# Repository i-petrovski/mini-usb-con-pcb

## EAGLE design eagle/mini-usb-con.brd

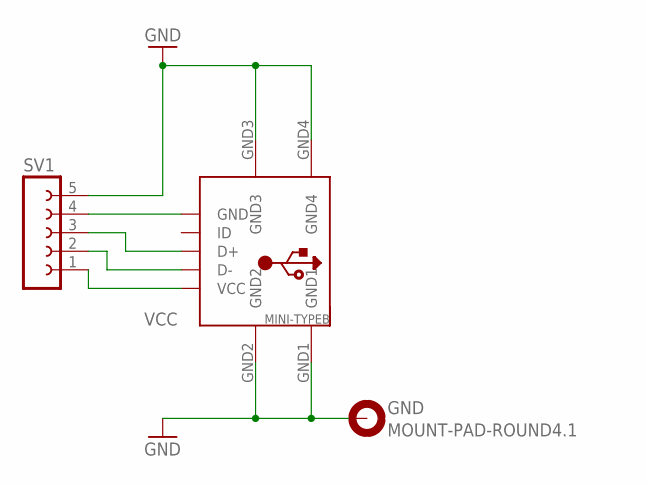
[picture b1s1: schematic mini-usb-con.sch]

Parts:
GND: MOUNT-PAD-ROUND4.1; 4,1-PAD
MINI-TYPEB: USBTHM; USB-MINIB-THM
SV1: FE05-1

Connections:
D+: MINI-TYPEB.D+, SV1.3
D-: MINI-TYPEB.D-, SV1.2
GND1: GND.B4,1, MINI-TYPEB.GND1, MINI-TYPEB.GND2, MINI-TYPEB.GND3, MINI-TYPEB.GND4, SV1.5
unnamed: MINI-TYPEB.GND, SV1.4
VCC: MINI-TYPEB.VCC, SV1.1

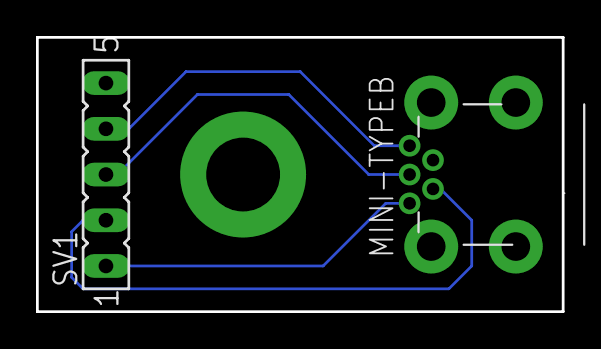
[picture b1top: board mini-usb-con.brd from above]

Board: 2 copper layers, 29.2 x 15.2 mm, 3 parts (0 on the bottom side), 5 nets.

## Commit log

2019-05-31 add pcb
